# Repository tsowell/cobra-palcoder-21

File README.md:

(Vezi [README-ro.md](README-ro.md) pentru o traducere greșită în română.)

# Cobra PAL Coder v2.1

These are KiCad files for the [PAL coder for the Cobra computer analyzed by
YO3GHM and described on cobrasov.com][PAL coder v2].

[PAL coder v2]: http://cobrasov.com/CoBra%20Project/pal2.html

The board connects to the PAL coder connector present on versions 0.2+ of the
motherboard, but it has an additional header, J2, on top to receive the VI
signal.  I use a one-pin ribbon cable to connect the PAL coder to the VI signal
on the video connector at the back of the motherboard.

The output PAL signal is passed through to the motherboard and also to an
optional BNC connector on the PAL board itself.

One notable modification to the version documented by YO3GHM is that this
version passes HB instead of NHB (because NHB is not on the PAL coder
connector) into the PROM, and the PROM contents must be different in order to
accomodate this.

Also, this revision uses the VCR signal from the motherboard instead of VNY.

NOTE: This revision has not been tested yet.  It includes some simple fixes for
problems in the [previous revision][5211970], which is known to work.

[5211970]: https://github.com/tsowell/cobra-palcoder-21/tree/5211970

## Images

The photograph is from the last revision with bodges.

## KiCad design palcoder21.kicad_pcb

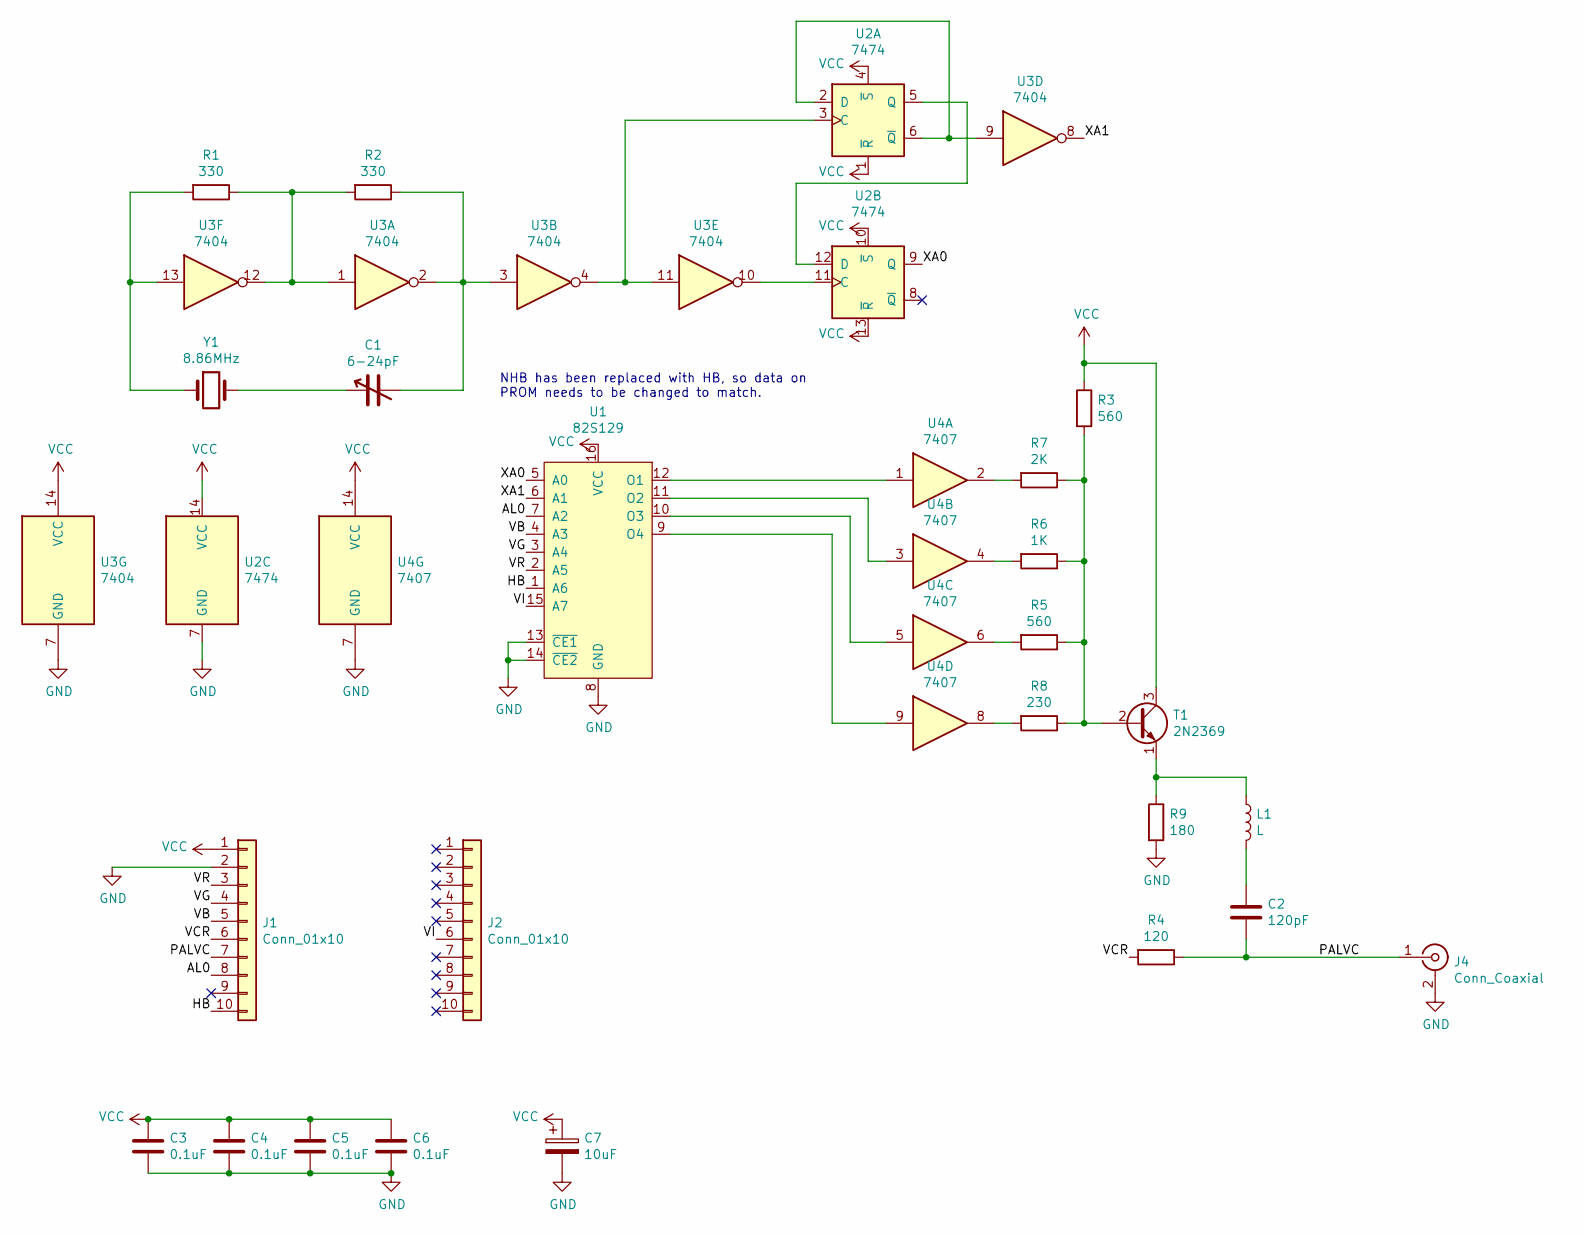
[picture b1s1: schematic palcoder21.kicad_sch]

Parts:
C1: 6-24pF; GYB27000
C2: 120pF; C_Disc_D5.1mm_W3.2mm_P5.00mm
C3, C4, C5, C6: 0.1uF; C_Disc_D5.1mm_W3.2mm_P5.00mm
C7: 10uF; CP_Radial_D5.0mm_P2.50mm
J1, J2: Conn_01x10; PinHeader_1x10_P2.54mm_Vertical
J4: Conn_Coaxial; BNC_TEConnectivity_BNC_TEConnectivity_5413558-1
L1: L; L_Axial_L9.5mm_D4.0mm_P15.24mm_Horizontal_Fastron_SMCC
R1, R2: 330; R_Axial_DIN0204_L3.6mm_D1.6mm_P7.62mm_Horizontal
R3, R5: 560; R_Axial_DIN0204_L3.6mm_D1.6mm_P7.62mm_Horizontal
R4: 120; R_Axial_DIN0204_L3.6mm_D1.6mm_P7.62mm_Horizontal
R6: 1K; R_Axial_DIN0204_L3.6mm_D1.6mm_P7.62mm_Horizontal
R7: 2K; R_Axial_DIN0204_L3.6mm_D1.6mm_P7.62mm_Horizontal
R8: 230; R_Axial_DIN0204_L3.6mm_D1.6mm_P7.62mm_Horizontal
R9: 180; R_Axial_DIN0204_L3.6mm_D1.6mm_P7.62mm_Horizontal
T1: 2N2369; TO-18-3
U1: 82S129; DIP-16_W7.62mm_Socket
U2: 7474; DIP-14_W7.62mm_Socket
U3: 7404; DIP-14_W7.62mm_Socket
U4: 7407; DIP-14_W7.62mm_Socket
Y1: 8.86MHz; Resonator-2Pin_W10.0mm_H5.0mm

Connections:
/AL0: J1.8, U1.7 (A2)
/HB: J1.10, U1.1 (A6)
/PALVC: C2.2, J1.7, J4.1 (In), R4.1
/VB: J1.5, U1.4 (A3)
/VCR: J1.6, R4.2
/VG: J1.4, U1.3 (A4)
/VI: J2.6, U1.15 (A7)
/VR: J1.3, U1.2 (A5)
/XA0: U1.5 (A0), U2.9 (Q)
/XA1: U1.6 (A1), U3.8
GND: C3.2, C4.2, C5.2, C6.2, C7.2, J1.2, J4.2 (Ext), R9.2, U1.8 (GND), U1.13 (~CE1), U1.14 (~CE2), U2.7 (GND), U3.7 (GND), U4.7 (GND)
unnamed: C1.1, Y1.2
unnamed: C1.2, R2.1, U3.2, U3.3
unnamed: C2.1, L1.2
unnamed: L1.1, R9.1, T1.1 (E)
unnamed: R1.1, R2.2, U3.1, U3.12
unnamed: R1.2, U3.13, Y1.1
unnamed: R3.2, R5.1, R6.1, R7.1, R8.1, T1.2 (B)
unnamed: R5.2, U4.6
unnamed: R6.2, U4.4
unnamed: R7.2, U4.2
unnamed: R8.2, U4.8
unnamed: U1.9 (O4), U4.9
unnamed: U1.10 (O3), U4.5
unnamed: U1.11 (O2), U4.3
unnamed: U1.12 (O1), U4.1
unnamed: U2.2 (D), U2.6 (~Q), U3.9
unnamed: U2.3 (C), U3.4, U3.11
unnamed: U2.11 (C), U3.10
unnamed: U2.5 (Q), U2.12 (D)
VCC: C3.1, C4.1, C5.1, C6.1, C7.1, J1.1, R3.1, T1.3 (C), U1.16 (VCC), U2.1 (~R), U2.4 (~S), U2.10 (~S), U2.13 (~R), U2.14 (VCC), U3.14 (VCC), U4.14 (VCC)

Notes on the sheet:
NHB has been replaced with HB, so data on PROM needs to be changed to match.

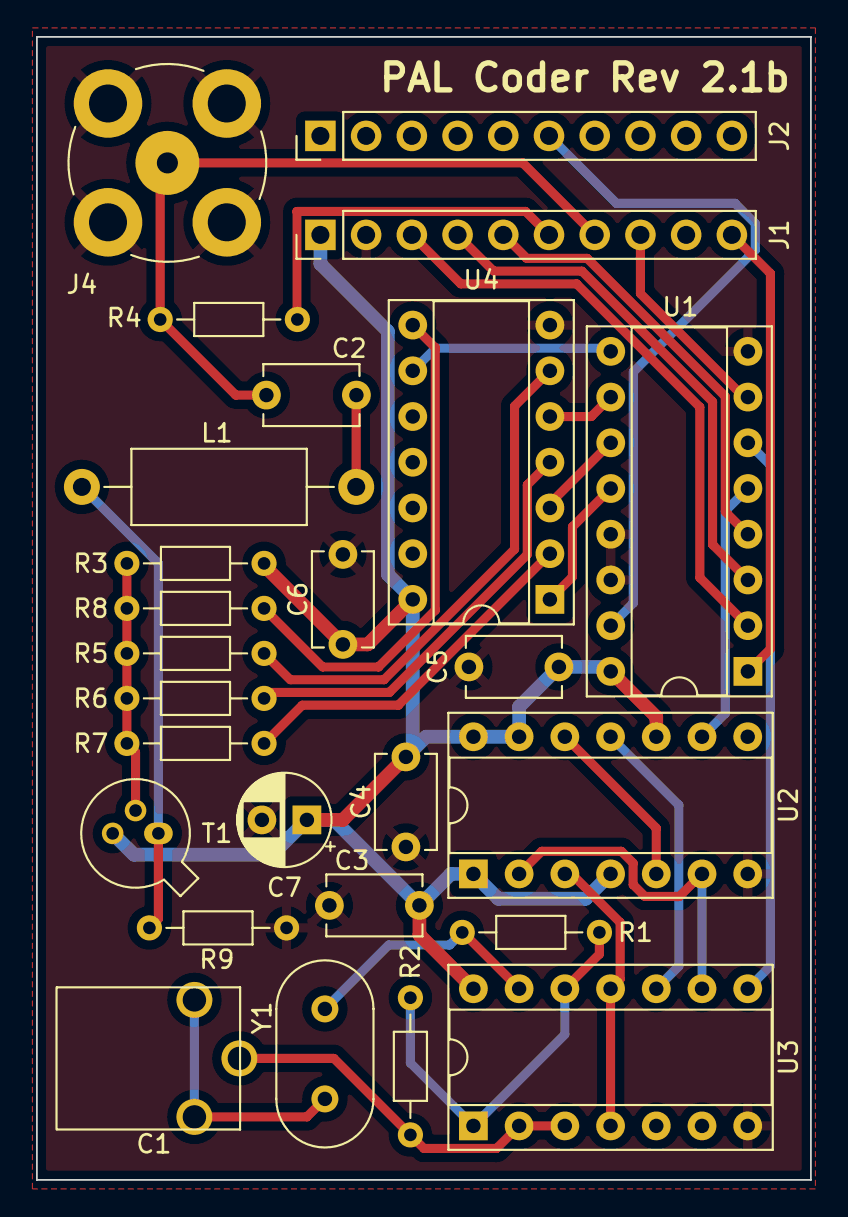
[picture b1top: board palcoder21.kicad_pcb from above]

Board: 2 copper layers, 43.0 x 63.5 mm, 26 parts (0 on the bottom side), 31 nets.

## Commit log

2022-02-02 Fix mistakes in first revision
    Add missing trace
    Fix swapped transistor pins
    Use VCR instead of VNY
